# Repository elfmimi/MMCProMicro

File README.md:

# ShiroMicro
ProMicro clone with Mid-Mount USB Type-C connector

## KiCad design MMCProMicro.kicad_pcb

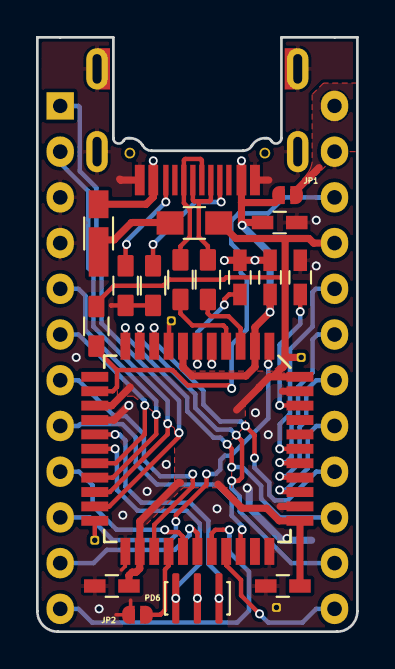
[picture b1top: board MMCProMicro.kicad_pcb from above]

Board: 2 copper layers, 17.8 x 33.0 mm, 24 parts (0 on the bottom side), 37 nets.

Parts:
C1: 4u7; C_0603_HandSoldering
C2: 1u0; C_0603_HandSoldering
C3, C4, C5, C6: 0u1; C_0603_HandSoldering
D1: D_Schottky; D_TUMD2_HandSoldering
F1: Fuse; F_0805_HandSoldering
J1: USB2_C_Receptacle; Mid_Mount-USB_C_HandSoldering
J2, J3: Conn_01x12; Pin_Header_Custom_Straight_1x12_Pitch2.54mm
JP1, JP2: SolderJumper_2_Open; SolderJumper-2_P1.0mm_Open_RoundedPad0.7x1.0mm
R1, R2: 5.1k; R_0603_HandSoldering
R3, R4: 22; R_0603_HandSoldering
R5: 10k; R_0603_HandSoldering
TP1, TP2, TP3, TP4: TestPoint; Measurement_Point_RoundSquare-TH_Tiny
U1: ATmega32U4-AU; TQFP-44_10x10mm_P0.8mm
X1: Resonator; Resonator_SMD_muRata_CSTxExxV-3Pin_3.0x1.1mm_HandSoldering_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

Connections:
/NC: J3.1, JP1.2
/PD6: JP2.2, U1.26
/UCAP: C2.1, U1.6
AREF: C4.1, U1.42
D+: R3.1, U1.4
D-: R4.1, U1.3
GND: C1.2, C2.2, C3.2, C4.2, C5.2, C6.2, J1.A1B12, J1.B1A12, J1.S1, J2.3, J2.4, J3.2, JP2.1, R1.1, R2.1, TP3.1, U1.5, U1.15, U1.23, U1.33, U1.35, U1.43, X1.2
unnamed: D1.1, F1.1
unnamed: J1.A5, R2.2
unnamed: J1.A6, J1.B6, R3.2
unnamed: J1.A7, J1.B7, R4.2
unnamed: J1.B5, R1.2
PB0: TP1.1, U1.8
PB1: J3.9, U1.9
PB2: J3.11, U1.10
PB3: J3.10, U1.11
PB4: J2.11, U1.28
PB5: J2.12, U1.29
PB6: J3.12, U1.30
PC6: J2.8, U1.31
PD0: J2.6, U1.18
PD1: J2.5, U1.19
PD2: J2.2, U1.20
PD3: J2.1, U1.21
PD4: J2.7, U1.25
PD5: TP2.1, U1.22
PD7: J2.9, U1.27
PE6: J2.10, U1.1
PF4: J3.5, U1.39
PF5: J3.6, U1.38
PF6: J3.7, U1.37
PF7: J3.8, U1.36
RESET: J3.3, R5.2, U1.13
VBUS: C1.1, C3.1, D1.2, J1.A4B9, J1.B4A9, JP1.1, U1.2, U1.7
VCC: C5.1, C6.1, F1.2, J3.4, R5.1, TP4.1, U1.14, U1.24, U1.34, U1.44
XTAL1: U1.17, X1.1
XTAL2: U1.16, X1.3

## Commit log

2019-04-28 Modified copyright author.
2019-04-28 Added .gitignore and .gitattributes
2019-04-28 Added filter attributes.
2019-04-28 Don't ignore *.lib files.
2019-04-28 Rev.A
2019-04-28 Rev.B
2019-04-28 Rev.C
2019-04-28 Rev.D
